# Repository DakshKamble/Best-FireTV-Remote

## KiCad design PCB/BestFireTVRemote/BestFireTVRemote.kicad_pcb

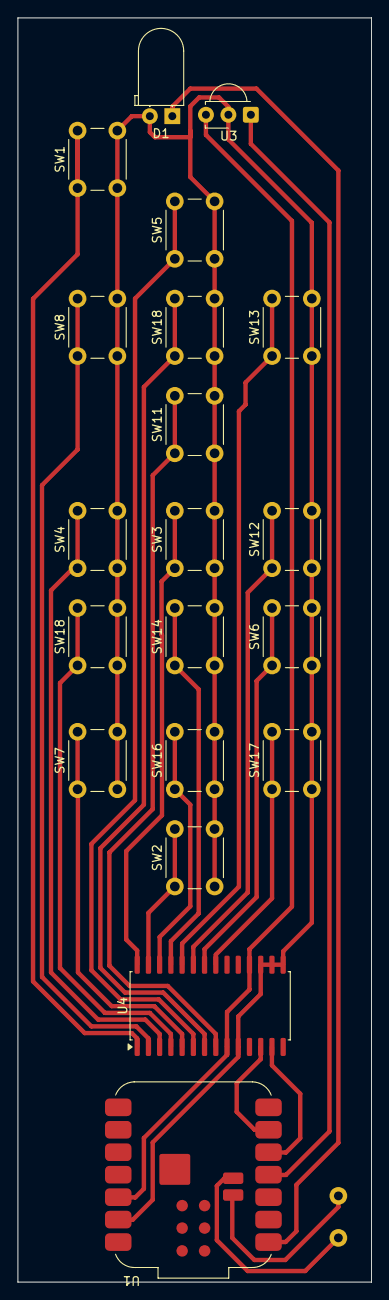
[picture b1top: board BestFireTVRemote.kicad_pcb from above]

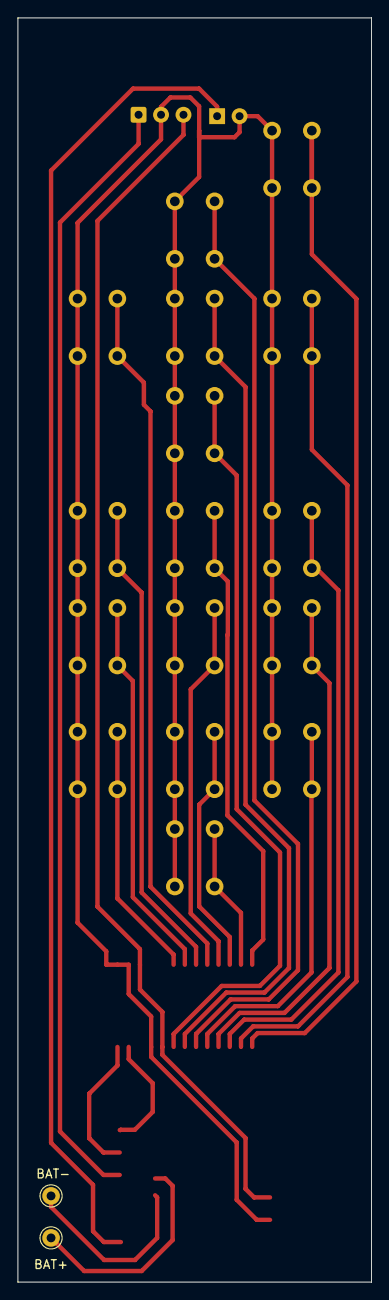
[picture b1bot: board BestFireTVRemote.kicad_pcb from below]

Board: 2 copper layers, 40.0 x 143.0 mm, 22 parts (2 on the bottom side), 24 nets.

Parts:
BAT+: Conn_01x01_Pin; Pin_D1.0mm_L10.0mm
BAT-: Conn_01x01_Pin; Pin_D1.0mm_L10.0mm
D1: LED; LED_D5.0mm_Horizontal_O1.27mm_Z3.0mm_Clear
SW1, SW2, SW3, SW4, SW5, SW6, SW7, SW8, SW11, SW12, SW13, SW14, SW16, SW17, SW18, SW18#2: SW_Push; SW_PUSH_6mm_H5mm
U1: XIAO-ESP32C3; MCU_Seeed_ESP32C3
U3: TSOP382xx; Vishay_MINICAST-3Pin
U4: MCP23017_SO; SOIC-28W_7.5x17.9mm_P1.27mm

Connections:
/GND: D1.2 (A), SW1.2, SW2.2, SW3.2, SW4.2, SW5.2, SW6.2, SW7.2, SW8.2, SW11.2, SW12.2, SW13.2, SW14.2, SW16.2, SW17.2, SW18.2, SW18#2.2, U1.13 (GND), U3.2 (GND), U4.10 (VSS), U4.15 (A0), U4.16 (A1), U4.17 (A2)
/Net-(U4-GPA0): SW17.1, U4.21 (GPA0)
/Net-(U4-GPA1): SW6.1, U4.22 (GPA1)
/Net-(U4-GPA2): SW12.1, U4.23 (GPA2)
/Net-(U4-GPA3): SW13.1, U4.24 (GPA3)
/Net-(U4-GPA4): SW14.1, U4.25 (GPA4)
/Net-(U4-GPA5): SW16.1, U4.26 (GPA5)
/Net-(U4-GPA6): SW2.1, U4.27 (GPA6)
/Net-(U4-GPA7): SW3.1, U4.28 (GPA7)
/Net-(U4-GPB0): SW1.1, U4.1 (GPB0)
/Net-(U4-GPB1): SW8.1, U4.2 (GPB1)
/Net-(U4-GPB2): SW4.1, U4.3 (GPB2)
/Net-(U4-GPB3): SW18.1, U4.4 (GPB3)
/Net-(U4-GPB4): SW7.1, U4.5 (GPB4)
/Net-(U4-GPB5): SW5.1, U4.6 (GPB5)
/Net-(U4-GPB6): SW18#2.1, U4.7 (GPB6)
/Net-(U4-GPB7): SW11.1, U4.8 (GPB7)
unnamed: BAT+.1, U1.16 (BAT+)
unnamed: BAT-.1, U1.17 (BAT-)
unnamed: D1.1 (K), U1.1 (D0)
unnamed: U1.12 (3V3), U3.3 (Vs), U4.9 (VDD), U4.18 (~RESET)
unnamed: U1.4 (D3), U3.1 (OUT)
unnamed: U1.5 (D4), U4.13 (SDA)
unnamed: U1.6 (D5), U4.12 (SCK)

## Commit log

2025-12-28 Working UP DOWN LEFT RIGHT navigation but no working VOLUME Functions
2025-12-31 Working up down left right and home button
2026-01-03 workig home
2026-01-04 Modified BLE keyboard library to add fastwforword rewind, all functions working
2026-01-04 complete pcb
